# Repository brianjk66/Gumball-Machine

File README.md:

# Gumball Drink Machine
By Brian Kaplan & Adam Elghor

[Project Demo](https://youtu.be/TyXLxnWFjBc)

## Project Idea
The idea of this project was to create an automated drink dispensing system centered around the mbed platform.  This project is intended to be an interactive system that mixes and dispenses internally stored drinks.  We wanted the system to resemble a gumball machine to give it a nice aesthetic and charm.

We decided to make the system gravity-fed for the sake of simplicity with the drinks being stored in a sphere at the top.  The drinks would then be dispensed via solenoid control valves into a cup at the base of the system.  The user interface to the system would be a [TFT LCD touchscreen](https://www.adafruit.com/product/2090) that a user can use to select the drink of their choice.

We also considered the use of [peristaltic pumps](https://www.adafruit.com/product/1150) for better liquid dispensing, a [liquid flow meter](https://www.adafruit.com/product/828) for better liquid measurement, and a [rotary encoder](https://www.adafruit.com/product/377) as an alternate user interface.  However, peristaltic pumps are costly (~$25 each), the flow meter was incredibly bulky and could not fit within the system, and the rotary encoder made for a confusing hybrid UI so we removed it as well.

## Hardware Setup

### Mechanical Components
The mechanical system consists of the following components:
- Handmade wooden body and lid
- 1ft Acrylic Sphere
- Assorted Color Water Beads
- 3ft Threaded Steel Dowel
- 2x Hex Nuts
- 2x Washers
- 4x Condiment Bottles
- 4x 12V Solenoid Valves (food-safe)
- Assorted Push-Fit Connecters and Fittings
- 10ft, 1/4" OD Polyethylene Tubing (food-safe)

### Electrical Components
The electrical system consists of the following components:
- Custom Printed Circuit Board:
  - mbed Microcontroller
  - 5V Linear Voltage Regulator
  - 3.3uF Ceramic Capacitor
  - 1.0uF Ceramic Capacitor
  - 4x 100 Ohm 1/4W Resistors
  - 4x 4.7k Ohm 1/4W Resistors
  - 4x 1N4001 Diodes
  - 4x N-Channel MOSFETs
  - Assorted 0.1" Male Headers
- 2.8in TFT LCD
- Flow Meter (Removed in final design)
- Rotary Encoder (Removed in final design)
- 12V, 2A Power Supply
- Barrel Jack
- Rocker Switch

## Code Setup
This system relies on using Adafruit's TFT LCD touchscreen on the mbed.  However, all of Adafruit's accompanying libraries and software support are made exclusively for Arduino (or Arduino-compatible) products.  As a result, the first major step in the software development of this project was porting the necessary Arduino libraries to the mbed.  The first library that we ported to mbed was [Adafruit's GFX Library](https://github.com/adafruit/Adafruit-GFX-Library) to provide us with a familiar graphics API.  The second library we ported was [Adafruit's ILI9341 Library](https://github.com/adafruit/Adafruit_ILI9341) for interfacing with the LCD.  The third library we ported was [Adafruit's FT6206 Library](https://github.com/adafruit/Adafruit_FT6206_Library) for interfacing with the FT6206 capacitive touch controller on the touchscreen.

Next, we wrote several test programs for testing the functionality of our hardware.  We wrote (and also used some existing) test programs for both the Arduino (before porting the libraries to mbed) and the mbed.  The Arduino test programs included a rotary encoder test, a flow meter test, and a couple LCD tests.  The mbed test programs included a flow sensor test and several LCD tests.

The final program that runs on the system is fairly straightforward.  It features 4 digital outputs for controlling each solenoid valve via a MOSFET.  There is also a touch controller and an LCD object for touchscreen I/O.  Finally a 2D array in program memory stores the hardcoded recipes for each drink.  The rows of the array correspond to recipes and the columns correspond to the proportion of each mixer in the drink.

The main loop body initializes all the peripherals as needed and sets up an interrupt routine for when a user touches the display.  If the user has selected an on-screen button corresponding to a drink, then the system dispenses the drink according to its recipe.  The dispensing routine starts a timer and opens the appropriate valves for durations that are directly proportional to the ratios provided in the recipe. The scaling factor (called TIME_SCALAR) must be calibrated based on the flow of drinks through the system

## Instructions

### Woodwork
The wooden body of the system was made by cutting several carefully measured trapezoids out of 8ft 2x4s and arranging them into 13 octagonal rings of decreasing size.  The rings were then glued together and stacked to form a conical structure.  This was then fastened to a lathe and turned down to the final shape of the system.  Cutouts were then made for the touchscreen and the cup hole.  The lid of the system was also turned on a lathe as well.

### The Sphere
The acrylic sphere had five holes drilled in it (one for structural support and 4 for tubing) and situated on top of the system.  The condiment bottles had holes drilled in their bases and had tubing fed in through the bottom and sealed with a combination of FDA-approved silicone sealant and hot glue.  The condiment bottles were placed in the sphere with the tubing passing through the previously mentioned holes and the lid was placed on top.  The threaded steel rod was cut to about 30" and fed through the lid, sphere, and bottom faceplate to serve as a central support column for the system, secured by a nut and washer on either side.

### Plumbing
The tubing assembly of the system consisted of the 4 solenoids connecting to the condiment bottles on one side.  On the other side, the solenoids connected to a set of Y-connectors to merge the 4 tubes into one for the output nozzle.  This tubing assembly was secured to the inside of the wooden body using hot glue.

### Electrical
The electrical system consisted primarily of a PCB.  The PCB took a 12V input for power and an onboard linear regulator to step the power down to 5V for the LCD and flow meter (which was later removed).  The PCB featured 4 driver sub-circuits to allow the mbed to open and close the solenoid valves (which used 12V power) via a DigitalOut pin.  The driver sub-circuits consisted of an N-channel MOSFET, a gate drive resistor, a gate pulldown resistor, and a fly-back diode.  The PCB connected touchscreen, the driver sub-circuits, the rotary encoder (removed), and the flow meter (removed) all to the appropriate mbed ports.  The PCB and touchscreen were mounted inside the body of the system using hot glue.

## Acknowledgements
We'd like to thank the PI's of the Invention Studio for all their help on this project and for providing us access to their incredible facilities for wood-working, metal-working, soldering, and PCB manufacturing.  We'd especially like to thank Morgan Cook, the Invention Studio's Director of Operations, for his continued help and support.

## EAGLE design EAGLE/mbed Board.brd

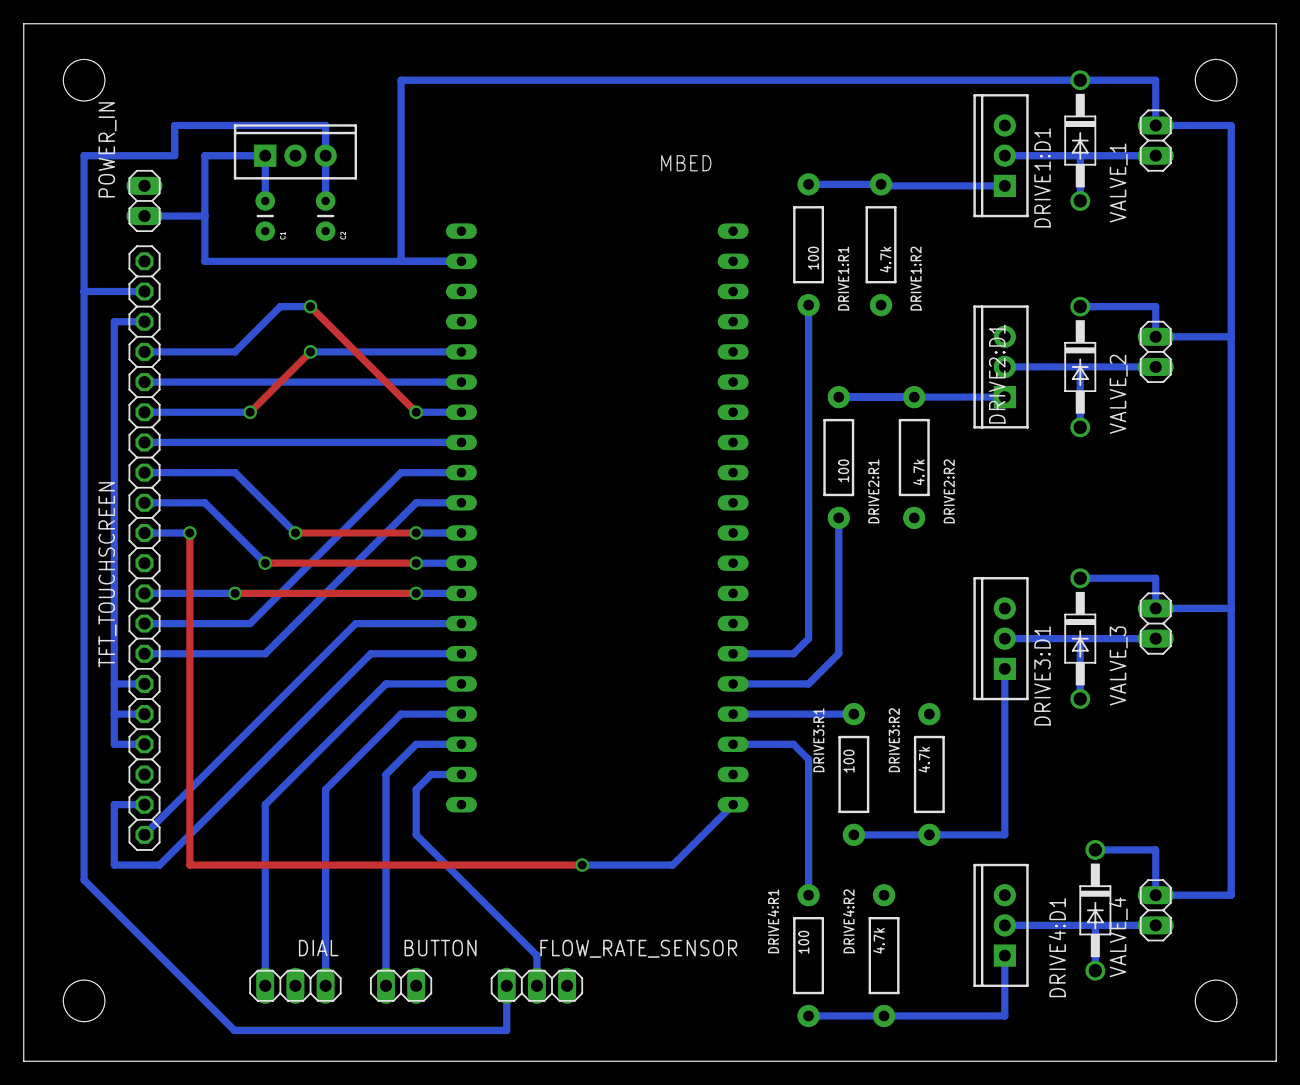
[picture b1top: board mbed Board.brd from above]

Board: 2 copper layers, 105.4 x 87.3 mm, 29 parts (0 on the bottom side), 32 nets.

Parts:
5V_REG: TO-220-SINK
BUTTON: 1X02
C1: 0.33uF; CAP-PTH-SMALL
C2: 0.1uF; CAP-PTH-SMALL
DIAL: 1X03
DRIVE1:D1, DRIVE2:D1, DRIVE3:D1, DRIVE4:D1: DO-41
DRIVE1:NFET, DRIVE2:NFET, DRIVE3:NFET, DRIVE4:NFET: N-CHANNEL_MOSFETGENERIC; TO-220-SINK
DRIVE1:R1, DRIVE2:R1, DRIVE3:R1, DRIVE4:R1: 100; AXIAL-0.4
DRIVE1:R2, DRIVE2:R2, DRIVE3:R2, DRIVE4:R2: 4.7k; AXIAL-0.4
FLOW_RATE_SENSOR: 1X03
MBED: MBED_NXP_LPC1768; MBED-KIT
POWER_IN: 1X02
TFT_TOUCHSCREEN: 1X20
VALVE_1, VALVE_2, VALVE_3, VALVE_4: 1X02

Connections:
3VO: TFT_TOUCHSCREEN.4, TFT_TOUCHSCREEN.5, TFT_TOUCHSCREEN.6, TFT_TOUCHSCREEN.18
5V: 5V_REG.3, C2.1, FLOW_RATE_SENSOR.1, TFT_TOUCHSCREEN.19
12V: 5V_REG.1, C1.1, DRIVE1:D1.C, DRIVE2:D1.C, DRIVE3:D1.C, DRIVE4:D1.C, MBED.VIN, POWER_IN.1, VALVE_1.1, VALVE_2.1, VALVE_3.1, VALVE_4.1
A: DIAL.1, MBED.P$16
B: DIAL.3, MBED.P$17
BUT: BUTTON.1, MBED.P$18
CARD_CS: MBED.P$15, TFT_TOUCHSCREEN.2
CARD_DETECT: MBED.P$14, TFT_TOUCHSCREEN.1
CLK: MBED.P$7, TFT_TOUCHSCREEN.17
CS: MBED.P$8, TFT_TOUCHSCREEN.14
DC: MBED.P$11, TFT_TOUCHSCREEN.13
DRIVE1:N$4: DRIVE1:NFET.1, DRIVE1:R1.P$1, DRIVE1:R2.P$1
DRIVE2:N$4: DRIVE2:NFET.1, DRIVE2:R1.P$1, DRIVE2:R2.P$1
DRIVE3:N$4: DRIVE3:NFET.1, DRIVE3:R1.P$1, DRIVE3:R2.P$1
DRIVE4:N$4: DRIVE4:NFET.1, DRIVE4:R1.P$1, DRIVE4:R2.P$1
DRIVE_1: DRIVE1:R1.P$2, MBED.P$26
DRIVE_2: DRIVE2:R1.P$2, MBED.P$25
DRIVE_3: DRIVE3:R1.P$2, MBED.P$24
DRIVE_4: DRIVE4:R1.P$2, MBED.P$23
FLOW: FLOW_RATE_SENSOR.2, MBED.P$19
GND: 5V_REG.2, BUTTON.2, C1.2, C2.2, DIAL.2, DRIVE1:NFET.3, DRIVE1:R2.P$2, DRIVE2:NFET.3, DRIVE2:R2.P$2, DRIVE3:NFET.3, DRIVE3:R2.P$2, DRIVE4:NFET.3, DRIVE4:R2.P$2, FLOW_RATE_SENSOR.3, MBED.GND, POWER_IN.2, TFT_TOUCHSCREEN.10, TFT_TOUCHSCREEN.20
IRQ: MBED.P$13, TFT_TOUCHSCREEN.9
LITE: MBED.P$21, TFT_TOUCHSCREEN.11
MISO: MBED.P$6, TFT_TOUCHSCREEN.16
MOSI: MBED.P$5, TFT_TOUCHSCREEN.15
unnamed: DRIVE2:D1.A, DRIVE2:NFET.2, VALVE_2.2
unnamed: DRIVE3:D1.A, DRIVE3:NFET.2, VALVE_3.2
unnamed: DRIVE4:D1.A, DRIVE4:NFET.2, VALVE_4.2
unnamed: DRIVE1:D1.A, DRIVE1:NFET.2, VALVE_1.2
RST: MBED.P$12, TFT_TOUCHSCREEN.12
SCL: MBED.P$10, TFT_TOUCHSCREEN.7
SDA: MBED.P$9, TFT_TOUCHSCREEN.8

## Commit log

2018-12-12 Wrote preliminary README
2018-12-12 Fixed some typos and re-worded some things
2018-12-12 Added all software and EAGLE files to repo
2018-12-12 Added some photos
2018-12-12 Added Adam's pictures and .gitignore
2018-12-12 Rearranged pictures and added electrical system pictures
2018-12-12 Last batch of pictures
2018-12-13 Added more pictures and labeled all pictures
2018-12-13 Added demo video to README and reorganized a bit
